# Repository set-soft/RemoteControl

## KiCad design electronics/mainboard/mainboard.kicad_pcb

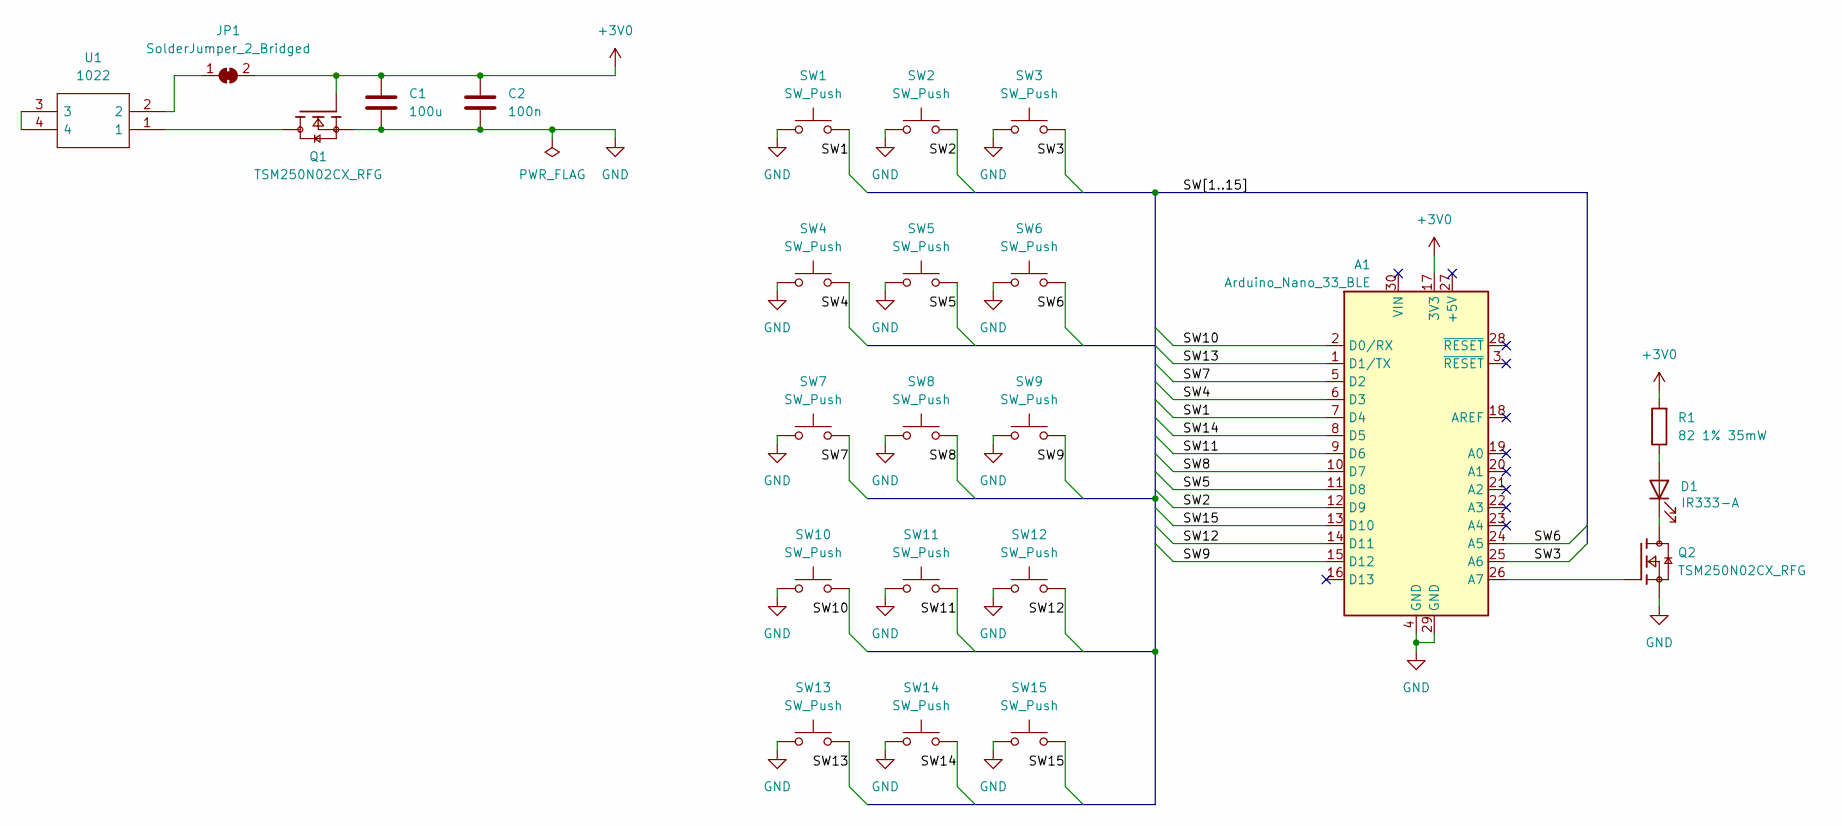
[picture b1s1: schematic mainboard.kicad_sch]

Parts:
A1: Arduino_Nano_33_BLE; Arduino_Nano_WithMountingHoles
C1: 100u; C_0805_2012Metric
C2: 100n; C_0805_2012Metric
D1: IR333-A; LED_D5.0mm_Horizontal_O1.27mm_Z3.0mm
JP1: SolderJumper_2_Bridged; SolderJumper-2_P1.3mm_Bridged_Pad1.0x1.5mm
Q1, Q2: TSM250N02CX_RFG; TRANS_TSM250N02CX_RFG; PARTREV A2007
R1: 82 1% 35mW; R_0805_2012Metric
SW1, SW2, SW3, SW4, SW5, SW6, SW7, SW8, SW9, SW10, SW11, SW12, SW13, SW14, SW15: SW_Push; SW_PUSH_6mm
U1: 1022; Mouser Part Number 534-1022

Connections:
+3V0: A1.17 (3V3), C1.1, C2.1, JP1.2 (B), Q1.1, R1.2
/SW1: A1.7 (D4), SW1.2
/SW2: A1.12 (D9), SW2.2
/SW3: A1.25 (A6), SW3.2
/SW4: A1.6 (D3), SW4.2
/SW5: A1.11 (D8), SW5.2
/SW6: A1.24 (A5), SW6.2
/SW7: A1.5 (D2), SW7.2
/SW8: A1.10 (D7), SW8.2
/SW9: A1.15 (D12), SW9.2
/SW10: A1.2 (D0/RX), SW10.2
/SW11: A1.9 (D6), SW11.2
/SW12: A1.14 (D11), SW12.2
/SW13: A1.1 (D1/TX), SW13.2
/SW14: A1.8 (D5), SW14.2
/SW15: A1.13 (D10), SW15.2
GND: A1.4 (GND), A1.29 (GND), C1.2, C2.2, Q1.2, Q2.2, SW1.1, SW2.1, SW3.1, SW4.1, SW5.1, SW6.1, SW7.1, SW8.1, SW9.1, SW10.1, SW11.1, SW12.1, SW13.1, SW14.1, SW15.1
unnamed: A1.26 (A7), Q2.1
unnamed: D1.1 (K), Q2.3
unnamed: D1.2 (A), R1.1
unnamed: JP1.1 (A), U1.2
unnamed: Q1.3, U1.1
unnamed: U1.3, U1.4

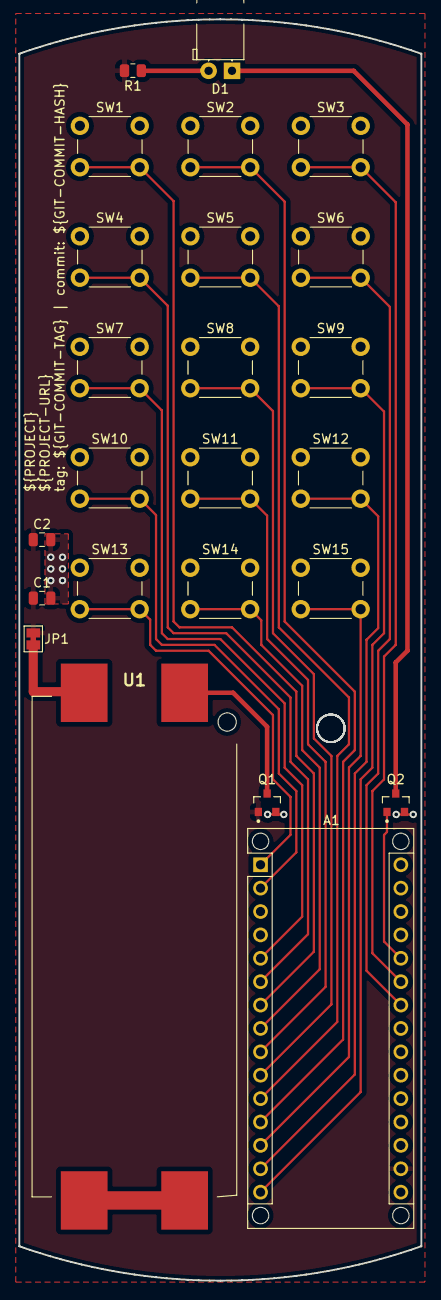
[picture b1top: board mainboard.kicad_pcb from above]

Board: 2 copper layers, 43.7 x 137.0 mm, 24 parts (0 on the bottom side), 23 nets.

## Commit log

2021-11-01 simple case
2021-12-16 add buttons to control led
2021-12-18 setup unit tests
2021-12-19 add cpputest code completion
2021-12-19 ignore cpputest folder
2021-12-19 corrected mock parameter names
2021-12-19 add unit tests for buttons
2022-03-14 minor changes to comply with latest turntable
2022-03-17 download cpputest into docker and some cleanup
2022-03-17 typedef byte
2022-03-17 remove no longer existend folder
2022-03-17 automatically added unwanted recommendation
2022-03-17 add IR remote lib
2022-03-19 first implementation of IR-Remote
2022-03-23 move constant to function
2022-03-23 bugfix
2022-03-24 move files as they are project specific
2022-03-24 add another include folder
2022-03-24 add missing functions
2022-03-24 move variable to better place
2022-03-24 add lib folder
2022-03-24 mock interrupts on/off functions
2022-03-24 add two more buttons
2022-04-02 integrate TV IR-remote
2022-04-02 remove interferences and make usable
2022-04-10 refactor
2022-04-10 fix typo
2022-04-10 add more functions
2022-04-10 remove classes
    Classes have been removed as this would have made functors necessary which rises problems with CPPUTEST.
2022-04-11 unit test Infra-Red
2022-04-11 add postfix 'test' to filename
2022-04-11 unit test buttons
2022-04-11 IrRemoteRaw rename to irRemoteRaw
2022-04-11 add missing source path
2022-04-11 unit tests
2022-04-12 add 'test' postfix
2022-04-12 unit test irRemoteHandler
2022-04-12 unit test turnTable
2022-04-12 'remoteControl' with tests
2022-04-12 add path to project sources so be found by IntelliSense
2022-04-15 use latest ble library
2022-04-15 improve and test turnTable tick
2022-05-14 integrate low power
2022-05-18 another idea for the case
2022-05-18 production files
2022-05-18 change material to petg
2022-05-19 add mainboard outline
2022-05-20 create electronics project
2022-05-20 integrate mainboard pcb
2022-05-20 add arduino nano to pcb
2022-05-20 add buttons and ir-led
2022-05-20 add schematic connections
2022-05-21 add polarity protection
2022-05-21 add hole for id-led
2022-05-21 add hole for ir led
2022-05-21 align buttons and ir-led
2022-05-23 add pin headers to 3d model of arduino
2022-05-23 update 3d models
2022-05-23 add pcb bottom support
2022-05-23 add pcb positioning pole
2022-05-23 add button holes
2022-05-26 add things for case mounting
2022-05-28 optimize case - different alignment - printing optimizations
2022-05-28 add support for LED
2022-06-04 modify closing mechanism and printing improvements - remove rounding (minkowski) for better printability - add closing mechanisms with levers => remove backring as no longer needed => remove position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
2022-06-05 clean up libraries and add more parts to desing - clean up libraries folder structure - no longer ignore important library table files - ignore auto save files - add fet for polarity protection - add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
2022-06-05 ignore more autosave files
2022-06-05 driver for ir-led and minor optimizations
2022-06-06 add buttons
2022-06-06 add variable layer height
2022-06-06 route pcb
2022-06-07 resolve drc errors and warnings
2022-06-07 clarify designator of arduino
2022-06-08 optimize position of designator JP1 und U1
2022-06-10 resolve ERC warnings and errors
2022-06-10 resolve drc warning by modifying footprint and removing exclusions
2022-06-10 add informations about project and version
2022-06-11 modify page layout with version data
2022-06-11 modify project informations
2022-06-11 Added verbosity
2022-06-11 Trying to trigger workflow
2022-06-11 Fixed WKS variables
